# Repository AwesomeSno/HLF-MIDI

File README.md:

# HLF-MIDI

A super slim, solid-state MIDI keyboard built with an ESP32-S3 that uses capacitive touch pads instead of mechanical switches. It plugs straight into any laptop, phone, or DAW as a plug-and-play USB-MIDI device.

---

## What is this?

Traditional MIDI keyboards are usually pretty bulky, full of plastic mechanisms, and annoying to carry around. For Hack Club's Half Life, I wanted to build something super flat and minimal: a solid-state MIDI keyboard with zero moving key parts, where the keys are literally etched onto the PCB in gold (ENIG).

Your fingers touch the pads directly, the ESP32-S3 detects the electric field change with its built-in hardware capacitive touch channels, and it immediately sends standard MIDI notes to your computer or synthesizer over native USB-C.

---

## How it works

1. **Capacitive Touch Keys**: Instead of mechanical switches, the 8 piano keys (C4 to C5) are exposed copper pads with an ENIG gold finish. When your finger gets close or touches a pad, it shifts the capacitance.
2. **ESP32-S3 Detection**: The ESP32-S3 reads all 8 touch channels in real time with hardware relaxation oscillators at sub-millisecond speeds.
3. **USB-MIDI Protocol**: When a key is tapped, the microcontroller sends standard MIDI Note On and Note Off packets over native Full-Speed USB. No drivers or extra software needed—it works automatically with Ableton, FL Studio, Logic, GarageBand, or web synths.
4. **Slide Fader & Rotary Knob**: A 45mm Bourns slide potentiometer lets you control pitch bend or modulation smoothly, while an EC11 rotary encoder handles filter cutoff or CC controls. You can also click the knob to toggle sustain.
5. **Octave Switching**: Dedicated tactile buttons let you shift up or down across octaves on the fly.
6. **Reverse-Mount NeoPixels**: 8 addressable RGB LEDs are mounted on the back of the board shining up through cutouts in the PCB, giving each key a clean ambient glow that reacts whenever you hit a note.

---

## Schematic & Hardware Design

The whole board was designed in KiCad with a clean 2-layer stackup:
- **MCU**: ESP32-S3-WROOM-1 (Xtensa dual-core @ 240MHz, native USB OTG, 14 capacitive touch channels)
- **Power**: 5V from USB-C stepped down to 3.3V through a low-noise TLV75533 LDO regulator
- **Protection**: USBLC6-2SC6 ultra-low capacitance TVS diode array protecting USB lines against ESD shocks
- **Board Dimensions**: 180mm × 75mm slim profile with 4mm corner radii and M3 mounting holes
- **Backlighting**: SK6812 MINI-E reverse-mount NeoPixels

All hardware design files are in the [`kicad/`](kicad/) directory:
- Schematic: [`kicad/hlf_midi.kicad_sch`](kicad/hlf_midi.kicad_sch) (and printable [`kicad/hlf_midi_schematic.pdf`](kicad/hlf_midi_schematic.pdf))
- PCB Layout: [`kicad/hlf_midi.kicad_pcb`](kicad/hlf_midi.kicad_pcb)
- Full Project: [`kicad/hlf_midi.kicad_pro`](kicad/hlf_midi.kicad_pro)
- Bill of Materials: [`kicad/bom.csv`](kicad/bom.csv)
- JLCPCB SMT Centroid: [`kicad/cpl.csv`](kicad/cpl.csv)
- Production Gerbers: [`kicad/hlf_midi_gerbers.zip`](kicad/hlf_midi_gerbers.zip)

---

## Firmware

The firmware is written in Arduino C++ for the ESP32-S3 using the native TinyUSB stack. It handles touch baseline calibration, exponential moving average (EMA) filtering for the analog slider to prevent jitter, and sends class-compliant MIDI packets at ~500Hz.

The code is available in [`firmware/hlf_midi_firmware/hlf_midi_firmware.ino`](firmware/hlf_midi_firmware/hlf_midi_firmware.ino).

---

## Getting Started

1. Open [`kicad/hlf_midi.kicad_pro`](kicad/hlf_midi.kicad_pro) in KiCad to view the full schematic and 3D PCB layout.
2. To flash the firmware, open [`firmware/hlf_midi_firmware/hlf_midi_firmware.ino`](firmware/hlf_midi_firmware/hlf_midi_firmware.ino) in Arduino IDE.
3. Select **ESP32S3 Dev Module**, enable **USB CDC On Boot** and **USB Mode: Hardware CDC and JTAG / TinyUSB**, and hit Upload.
4. Plug it into your computer via USB-C, launch your favorite DAW, and start playing!

---

## Author

Designed and built by **Harinandan J V** for Hack Club's Half Life hardware program.

## Open Source

This project is completely open source under the MIT License. Feel free to use, modify, or build upon it for your own synths and music gear!

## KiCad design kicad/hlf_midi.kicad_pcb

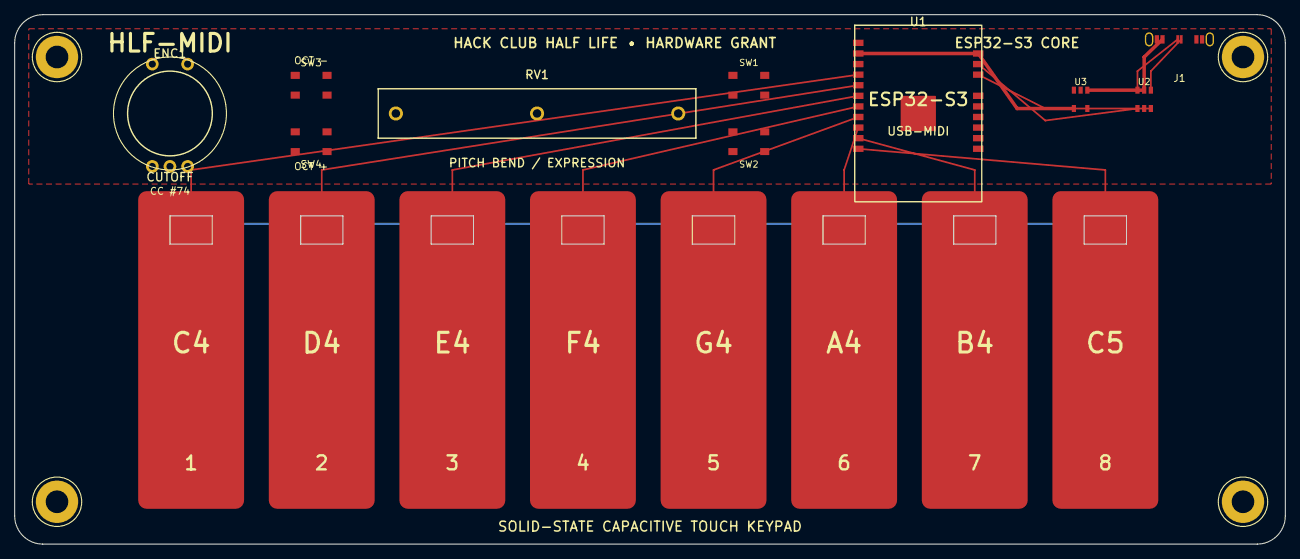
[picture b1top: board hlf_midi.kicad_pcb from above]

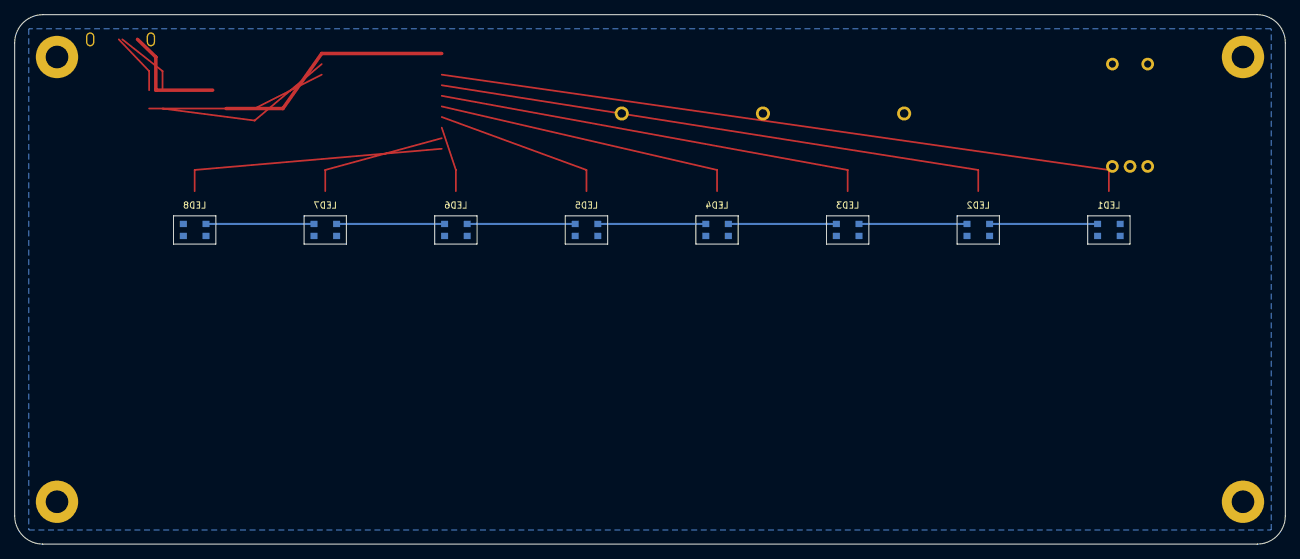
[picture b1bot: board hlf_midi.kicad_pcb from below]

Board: 2 copper layers, 180.0 x 75.0 mm, 18 parts (8 on the bottom side), 14 nets.

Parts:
ENC1: EC11_Knob; RotaryEncoder_Alps_EC11E-Switch_Vertical_H20mm
J1: USB_C_Receptacle_HRO_TYPE-C-31-M-12
LED1, LED2, LED3, LED4, LED5, LED6, LED7, LED8: SK6812MINI-E; LED_SK6812MINI-E
RV1: Potentiometer_Bourns_PTA4543_Single_Slide
SW1, SW2, SW3, SW4: SW_SPST_TL3342
U1: ESP32-S3-WROOM-1
U2: SOT-23-6
U3: SOT-23-5

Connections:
+3V3: RV1.1, U1.2, U3.5
+5V: J1.A4, J1.B9, LED1.1, LED2.1, LED3.1, LED4.1, LED5.1, LED6.1, LED7.1, LED8.1, U2.5, U3.1, U3.3
ADC_FADER: RV1.2, U1.15
BOOT: SW2.1, SW2.3
EN: SW1.1, SW1.3, U1.3
ENC_A: ENC1.A, U1.12
ENC_B: ENC1.B, U1.13
ENC_SW: ENC1.S1, U1.14
GND: ENC1.C, ENC1.S2, J1.A1, J1.B12, J1.SH, LED1.3, LED2.3, LED3.3, LED4.3, LED5.3, LED6.3, LED7.3, LED8.3, RV1.3, SW1.2, SW1.4, SW2.2, SW2.4, SW3.2, SW3.4, SW4.2, SW4.4, U1.1, U1.EP, U2.2, U3.2
LED_DATA: LED1.2, LED1.4, LED2.2, LED2.4, LED3.2, LED3.4, LED4.2, LED4.4, LED5.2, LED5.4, LED6.2, LED6.4, LED7.2, LED7.4, LED8.2, LED8.4, U1.24
OCT_DOWN: SW3.1, SW3.3, U1.16
OCT_UP: SW4.1, SW4.3, U1.17
USB_D_N: J1.A7, U1.22, U2.3, U2.4
USB_D_P: J1.A6, U1.23, U2.1, U2.6

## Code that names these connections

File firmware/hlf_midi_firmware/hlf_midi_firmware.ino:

/*
 * HLF-MIDI - ESP32-S3 Solid-State Capacitive Touch MIDI Controller
 * Built for Hack Club's Half Life Hardware Grant
 * 
 * Hardware Pinout:
 * - Touch Keys 1-8: GPIO 1 to 8 (C4 through C5)
 * - EC11 Rotary Encoder: GPIO 9 (A), GPIO 10 (B), GPIO 11 (Switch)
 * - Slide Fader: GPIO 12 (ADC1 Channel 1)
 * - Octave Switches: GPIO 13 (Down), GPIO 14 (Up)
 * - SK6812 NeoPixels: GPIO 21 (8x reverse-mount addressable RGB)
 * - Native USB: GPIO 19 (D-), GPIO 20 (D+)
 */

#include <Arduino.h>
#include "USB.h"
#include "USBMIDI.h"
#include <Adafruit_NeoPixel.h>

USBMIDI MIDI;

// Hardware Pin Definitions
const int TOUCH_PINS[8] = {1, 2, 3, 4, 5, 6, 7, 8};
const int ENC_PIN_A = 9;
const int ENC_PIN_B = 10;
const int ENC_SW_PIN = 11;
const int FADER_ADC_PIN = 12;
const int OCT_DOWN_PIN = 13;
const int OCT_UP_PIN = 14;
const int NEOPIXEL_PIN = 21;
const int NUM_KEYS = 8;

Adafruit_NeoPixel leds(NUM_KEYS, NEOPIXEL_PIN, NEO_GRB + NEO_KHZ800);

// Capacitive Touch State & Calibration
uint32_t touchBaseline[8] = {0};
bool keyActive[8] = {false};
const uint32_t TOUCH_HYSTERESIS_DROP = 4500; // Calibrated drop threshold

// Musical Scale Configuration
int currentOctave = 4; // Default C4 octave
const uint8_t SCALE_INTERVALS[8] = {0, 2, 4, 5, 7, 9, 11, 12}; // Major scale C to C

// Rotary Encoder State
volatile int encoderPos = 64; // CC 0-127 centered
int lastEncoderPos = 64;
int lastEncAState = HIGH;

// Fader / Modulation State
int lastFaderMidiVal = -1;
uint32_t faderSmoothEMA = 0;

// LED Color Palettes per Octave
const uint32_t OCTAVE_COLORS[7] = {
  0x00FF88, // C2 - Mint
  0x00D4FF, // C3 - Cyan
  0x7000FF, // C4 - Violet
  0xFF007F, // C5 - Magenta
  0xFF5500, // C6 - Amber
  0xFAFF00, // C7 - Gold
  0xFFFFFF  // C8 - Diamond White
};

void IRAM_ATTR readEncoderISR() {
  int aState = digitalRead(ENC_PIN_A);
  int bState = digitalRead(ENC_PIN_B);
  if (aState != lastEncAState && aState == LOW) {
    if (bState != aState) {
      if (encoderPos < 127) encoderPos++;
    } else {
      if (encoderPos > 0) encoderPos--;
    }
  }
  lastEncAState = aState;
}

void calibrateTouchSensors() {
  // Collect 64 baseline samples while untouched
  for (int sample = 0; sample < 64; sample++) {
    for (int i = 0; i < NUM_KEYS; i++) {
      touchBaseline[i] += touchRead(TOUCH_PINS[i]);
    }
    delay(5);
  }
  for (int i = 0; i < NUM_KEYS; i++) {
    touchBaseline[i] /= 64;
  }
}

void setup() {
  Serial.begin(115200);

  // Initialize USB-MIDI stack
  MIDI.begin();
  USB.begin();

  // Pin Modes
  pinMode(ENC_PIN_A, INPUT_PULLUP);
  pinMode(ENC_PIN_B, INPUT_PULLUP);
  pinMode(ENC_SW_PIN, INPUT_PULLUP);
  pinMode(OCT_DOWN_PIN, INPUT_PULLUP);
  pinMode(OCT_UP_PIN, INPUT_PULLUP);
  analogReadResolution(12);

  attachInterrupt(digitalPinToInterrupt(ENC_PIN_A), readEncoderISR, CHANGE);

  // Initialize LEDs
  leds.begin();
  leds.setBrightness(40); // 15% brightness for slim thermal budget
  for (int i = 0; i < NUM_KEYS; i++) {
    leds.setPixelColor(i, OCTAVE_COLORS[currentOctave - 2]);
  }
  leds.show();

  // Calibrate touch sensors
  calibrateTouchSensors();
}

void loop() {
  // 1. Scan Capacitive Touch Keys
  for (int i = 0; i < NUM_KEYS; i++) {
    uint32_t val = touchRead(TOUCH_PINS[i]);
    bool isTouched = (val < (touchBaseline[i] - TOUCH_HYSTERESIS_DROP));
    uint8_t midiNote = (currentOctave * 12) + SCALE_INTERVALS[i];

    if (isTouched && !keyActive[i]) {
      keyActive[i] = true;
      MIDI.noteOn(midiNote, 100, 1); // Note on, velocity 100, channel 1
      leds.setPixelColor(i, 0xFFFFFF); // Glow white on strike
      leds.show();
    } else if (!isTouched && keyActive[i]) {
      keyActive[i] = false;
      MIDI.noteOff(midiNote, 0, 1);
      leds.setPixelColor(i, OCTAVE_COLORS[currentOctave - 2]); // Return to octave accent
      leds.show();
    }
  }

  // 2. Rotary Encoder -> MIDI CC #74 (Brightness / Filter Cutoff)
  if (encoderPos != lastEncoderPos) {
    lastEncoderPos = encoderPos;
    MIDI.controlChange(74, encoderPos, 1);
  }

  // 3. Encoder Push Switch -> MIDI CC #64 (Sustain Pedal)
  static bool lastSwState = HIGH;
  bool swState = digitalRead(ENC_SW_PIN);
  if (swState != lastSwState) {
    lastSwState = swState;
    if (swState == LOW) {
      MIDI.controlChange(64, 127, 1); // Sustain on
    } else {
      MIDI.controlChange(64, 0, 1);   // Sustain off
    }
  }

  // 4. Slide Potentiometer -> MIDI Pitch Bend
  uint32_t rawAdc = analogRead(FADER_ADC_PIN);
  faderSmoothEMA = (faderSmoothEMA * 7 + rawAdc) >> 3; // 8-point EMA jitter filter
  int faderVal = map(faderSmoothEMA, 0, 4095, -8192, 8191);
  static int lastPitchBend = 0;
  if (abs(faderVal - lastPitchBend) > 64) {
    lastPitchBend = faderVal;
    MIDI.pitchBend(faderVal, 1);
  }

  // 5. Octave Buttons
  static unsigned long lastBtnTime = 0;
  if (millis() - lastBtnTime > 180) {
    if (digitalRead(OCT_DOWN_PIN) == LOW && currentOctave > 2) {
      currentOctave--;
      lastBtnTime = millis();
      for (int i = 0; i < NUM_KEYS; i++) {
        leds.setPixelColor(i, OCTAVE_COLORS[currentOctave - 2]);
      }
      leds.show();
    } else if (digitalRead(OCT_UP_PIN) == LOW && currentOctave < 8) {
      currentOctave++;
      lastBtnTime = millis();
      for (int i = 0; i < NUM_KEYS; i++) {
        leds.setPixelColor(i, OCTAVE_COLORS[currentOctave - 2]);
      }
      leds.show();
    }
  }

  delay(2); // ~500Hz loop rate
}
